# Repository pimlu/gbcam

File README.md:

## Gameboy Camera webcam

This project turns the "eyeball" of the Gameboy Camera into a webcam.

## PCB design

Made in KiCad, check out the boards directory.

## Building, flashing

Run `source setup.sh`, then `./flash.sh`. You can run `./serial.sh` in another tab to show the log output. `./flash.sh` will wait until it sees the device (you have to press down BOOTSEL + RESET).

## MacOS eject notifications
Adafruit has a [wonderful blog](https://blog.adafruit.com/2021/05/11/how-to-tone-down-macos-big-surs-circuitpy-eject-notifications/) showing you how to tone down the annoying "disk ejected unsafely" notifications. It doesn't remove it but at least they auto-dismiss.

## Important assembly note

In rev1, the footprint for the JST connector (the one hooked up to the gameboy camera) is backwards. It needs to be turned 180 - fortunately there is just barely enough clearance that the board still works if you flip it around.

## Pinout

See pinout.h

## Component docs

SHARP LS013B7DH05: [Programming Sharp’s Memory LCDs](https://www.sharpsde.com/fileadmin/products/Displays/2016_SDE_App_Note_for_Memory_LCD_programming_V1.3.pdf)

M64283FP (GB Camera): No official online datasheet (it's from the 90s) but there are sources available. [MITSUBISHI Image Sensor (Artificial Retina Chip)](https://github.com/Raphael-Boichot/Play-with-the-Game-Boy-Camera-Mitsubishi-M64282FP-sensor/blob/main/Additionnal%20informations/Mitsubishi%20Integrated%20Circuit%20M64283FP%20Image%20Sensor.pdf)

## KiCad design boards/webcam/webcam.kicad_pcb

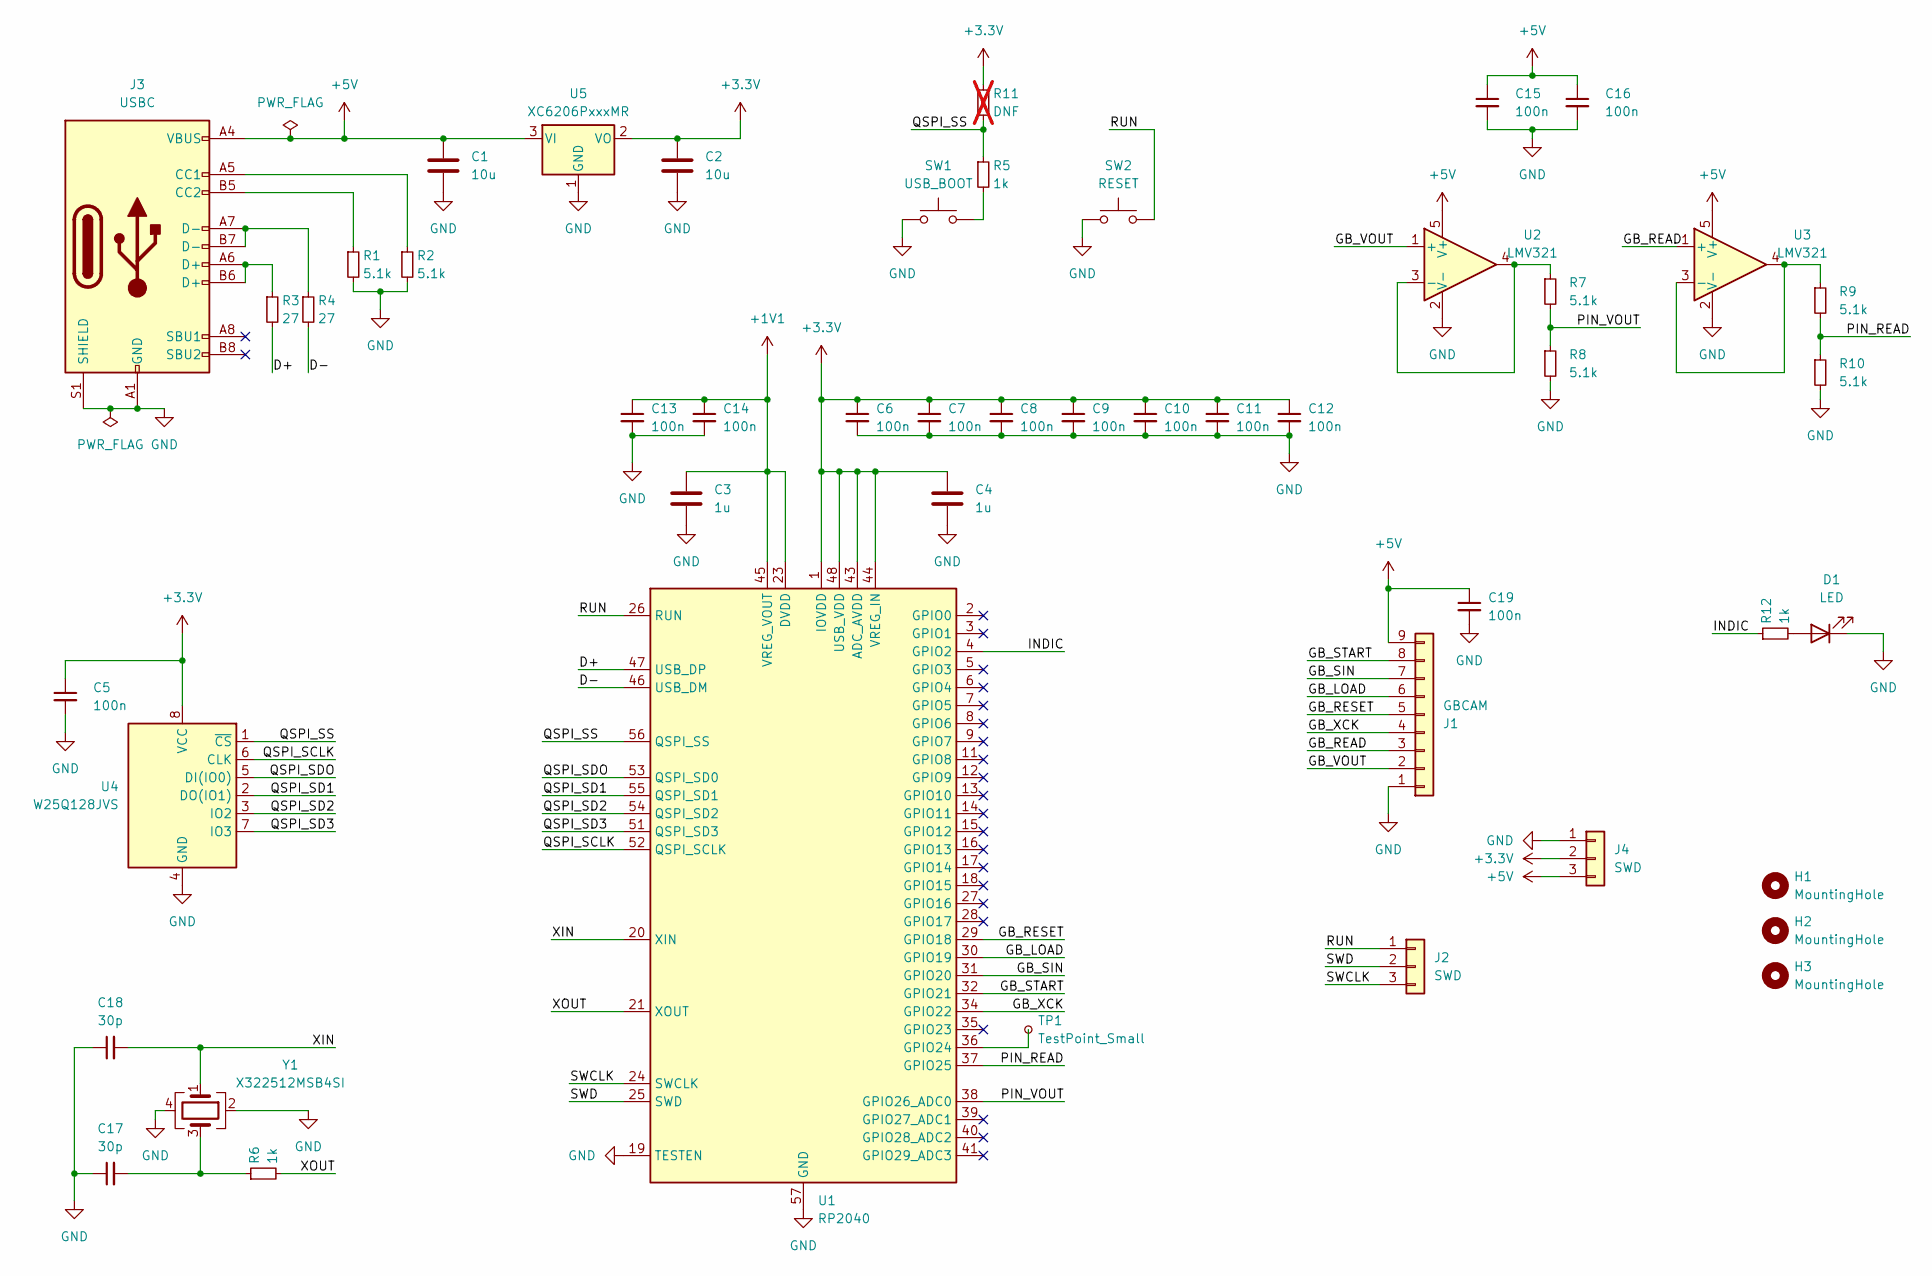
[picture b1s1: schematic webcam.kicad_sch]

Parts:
C1, C2: 10u; C_0603_1608Metric; LCSC C96446
C3, C4: 1u; C_0402_1005Metric; LCSC C52923
C5, C6, C7, C8, C9, C10, C11, C12, C13, C14, C15, C16, C19: 100n; C_0402_1005Metric; LCSC C1525
C17, C18: 30p; C_0402_1005Metric; LCSC C1570
D1: LED; LED_0805_2012Metric; LCSC C84256
H1, H2, H3: MountingHole; gbcam_mount
J1: GBCAM; JST_ZH-9
J2, J4: SWD; PinHeader_1x03_P1.00mm_Vertical
J3: USBC; JLCPCB_USB_C_Receptacle_HRO_TYPE-C-31-M-12; LCSC C165948
R1, R2, R7, R8, R9, R10: 5.1k; R_0402_1005Metric; LCSC C25905
R3, R4: 27; R_0603_1608Metric; LCSC C25190
R5, R6, R12: 1k; R_0402_1005Metric; LCSC C11702
R11: DNF; R_0402_1005Metric; not fitted
SW1: USB_BOOT; SW_Push_1P1T_XKB_TS-1187A; LCSC C318884
SW2: RESET; SW_Push_1P1T_XKB_TS-1187A; LCSC C318884
TP1: TestPoint_Small; TestPoint_THTPad_D1.0mm_Drill0.5mm
U1: RP2040; QFN-56-1EP_7x7mm_P0.4mm_EP3.2x3.2mm; LCSC C2040
U2, U3: LMV321; SOT-23-5; LCSC C7972
U4: W25Q128JVS; SOIC-8_5.23x5.23mm_P1.27mm; LCSC C97521
U5: XC6206PxxxMR; SOT-23-3; LCSC C5446
Y1: X322512MSB4SI; Crystal_SMD_3225-4Pin_3.2x2.5mm; LCSC C9002

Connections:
+1V1: C3.1, C13.1, C14.1, U1.23 (DVDD), U1.45 (VREG_VOUT), U1.50 (DVDD)
+3.3V: C2.1, C4.1, C5.1, C6.1, C7.1, C8.1, C9.1, C10.1, C11.1, C12.1, J4.2, R11.1, U1.1 (IOVDD), U1.10 (IOVDD), U1.22 (IOVDD), U1.33 (IOVDD), U1.42 (IOVDD), U1.43 (ADC_AVDD), U1.44 (VREG_IN), U1.48 (USB_VDD), U1.49 (IOVDD), U4.8 (VCC), U5.2 (VO)
+5V: C1.1, C15.1, C16.1, C19.1, J1.9, J3.A4 (VBUS), J3.A9 (VBUS), J3.B4 (VBUS), J3.B9 (VBUS), J4.3, U2.5 (V+), U3.5 (V+), U5.3 (VI)
/D+: R3.2, U1.47 (USB_DP)
/D-: R4.2, U1.46 (USB_DM)
/GB_LOAD: J1.6, U1.30 (GPIO19)
/GB_READ: J1.3, U3.1 (+)
/GB_RESET: J1.5, U1.29 (GPIO18)
/GB_SIN: J1.7, U1.31 (GPIO20)
/GB_START: J1.8, U1.32 (GPIO21)
/GB_VOUT: J1.2, U2.1 (+)
/GB_XCK: J1.4, U1.34 (GPIO22)
/INDIC: R12.1, U1.4 (GPIO2)
/PIN_READ: R9.2, R10.1, U1.37 (GPIO25)
/PIN_VOUT: R7.2, R8.1, U1.38 (GPIO26_ADC0)
/QSPI_SCLK: U1.52 (QSPI_SCLK), U4.6 (CLK)
/QSPI_SD1: U1.55 (QSPI_SD1), U4.2 (DO(IO1))
/QSPI_SD2: U1.54 (QSPI_SD2), U4.3 (IO2)
/QSPI_SD3: U1.51 (QSPI_SD3), U4.7 (IO3)
/QSPI_SDO: U1.53 (QSPI_SD0), U4.5 (DI(IO0))
/QSPI_SS: R5.1, R11.2, U1.56 (QSPI_SS), U4.1 (~CS)
/RUN: J2.1, SW2.2, U1.26 (RUN)
/SWCLK: J2.3, U1.24 (SWCLK)
/SWD: J2.2, U1.25 (SWD)
/XIN: C18.2, U1.20 (XIN), Y1.1
/XOUT: R6.2, U1.21 (XOUT)
GND: C1.2, C2.2, C3.2, C4.2, C5.2, C6.2, C7.2, C8.2, C9.2, C10.2, C11.2, C12.2, C13.2, C14.2, C15.2, C16.2, C17.1, C18.1, C19.2, D1.1 (K), J1.1, J3.A1 (GND), J3.A12 (GND), J3.B1 (GND), J3.B12 (GND), J3.S1 (SHIELD), J4.1, R1.2, R2.2, R8.2, R10.2, SW1.1, SW2.1, U1.19 (TESTEN), U1.57 (GND), U2.2 (V-), U3.2 (V-), U4.4 (GND), U5.1 (GND), Y1.2, Y1.4
unnamed: C17.2, R6.1, Y1.3
unnamed: D1.2 (A), R12.2
unnamed: J3.A5 (CC1), R2.1
unnamed: J3.B5 (CC2), R1.1
unnamed: J3.A6 (D+), J3.B6 (D+), R3.1
unnamed: J3.A7 (D-), J3.B7 (D-), R4.1
unnamed: R5.2, SW1.2
unnamed: TP1.1, U1.36 (GPIO24)
unnamed: R7.1, U2.3 (-), U2.4
unnamed: R9.1, U3.3 (-), U3.4

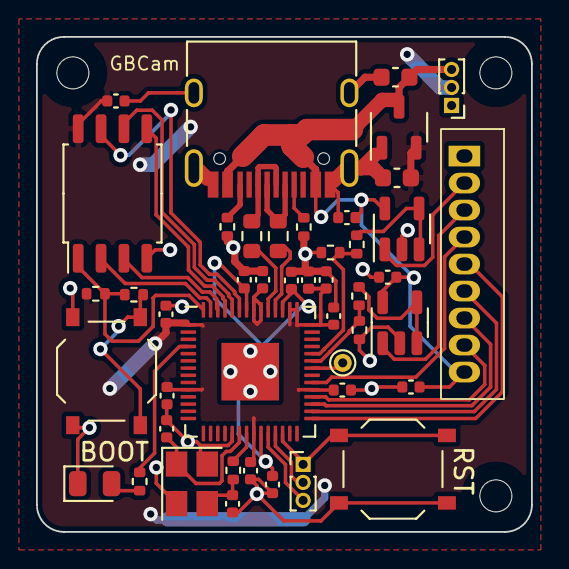
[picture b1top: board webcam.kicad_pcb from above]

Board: 2 copper layers, 27.5 x 27.5 mm, 48 parts (0 on the bottom side), 37 nets.

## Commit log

2022-11-21 initial commit
    I think this is as good as I can get it without SWD.
2022-11-21 sharp: get sharp display flashing
2022-11-28 add to README
2023-06-13 more camera stuff, rearrange to new folder structure
2023-06-14 cam: add initialization logic for the gbcam
    Might have to sleep since the mcu is too fast
2023-06-15 gbcam: get sampling/clocks going
    Haven't tested it on the real camera but it's close.
    The RP2040 is really amazing
2023-06-17 gbcam: get it working!
2023-06-24 kicad: create the gbcam pcb
2023-06-25 pcb: prepare for jlcpcb
2023-06-25 pcb: final prep for jlcpcb
2023-07-07 build: quality of life improvements
2023-07-08 usb: get serial with handrolled tinyusb working
2023-07-08 build: clean stuff up
2023-07-09 usb: get video working
2023-07-09 gbcam: get it... kind of working
2023-07-10 webcam: improve visual quality
2023-07-14 gbcam: lower exposure time
2023-07-14 gbcam: make it work on the pcb
    yay!
2023-07-15 webcam: add auto white balance, cleaner logs
2023-07-15 gbcam: document whitebalance
